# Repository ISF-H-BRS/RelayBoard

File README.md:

# ISF Relay Board

## Introduction
This repository contains schematics, PCB layout, firmware and software for a circuit board providing 16 software-programmable solid-state relays with individual voltage and current monitoring, every channel capable of switching up to 2 A at 32 V. It's original purpose was to allow control of various valves and pumps for chemical processes from within a LabVIEW program but it may also be useful for other automated control tasks.

## Usage
The device uses a simple text-based protocol to communicate over a USB serial port. See Firmware/Protocol.txt for details. The protocol is also wrapped in a software library exposing both C++ and C interfaces, designed to allow it to be used from any programming language, including LabVIEW.

A Qt-based graphical example program is also provided that can be used to manually test all features of the device.

## License
All source code for the software and firmware components, including the LabVIEW code, is licensed under the terms of the GNU General Public License (GPL). All schematics and layout files are licensed under the terms of the Creative Commons Attribution-ShareAlike International Public License (CC BY-SA). See COPYING in the respective subdirectories for details.

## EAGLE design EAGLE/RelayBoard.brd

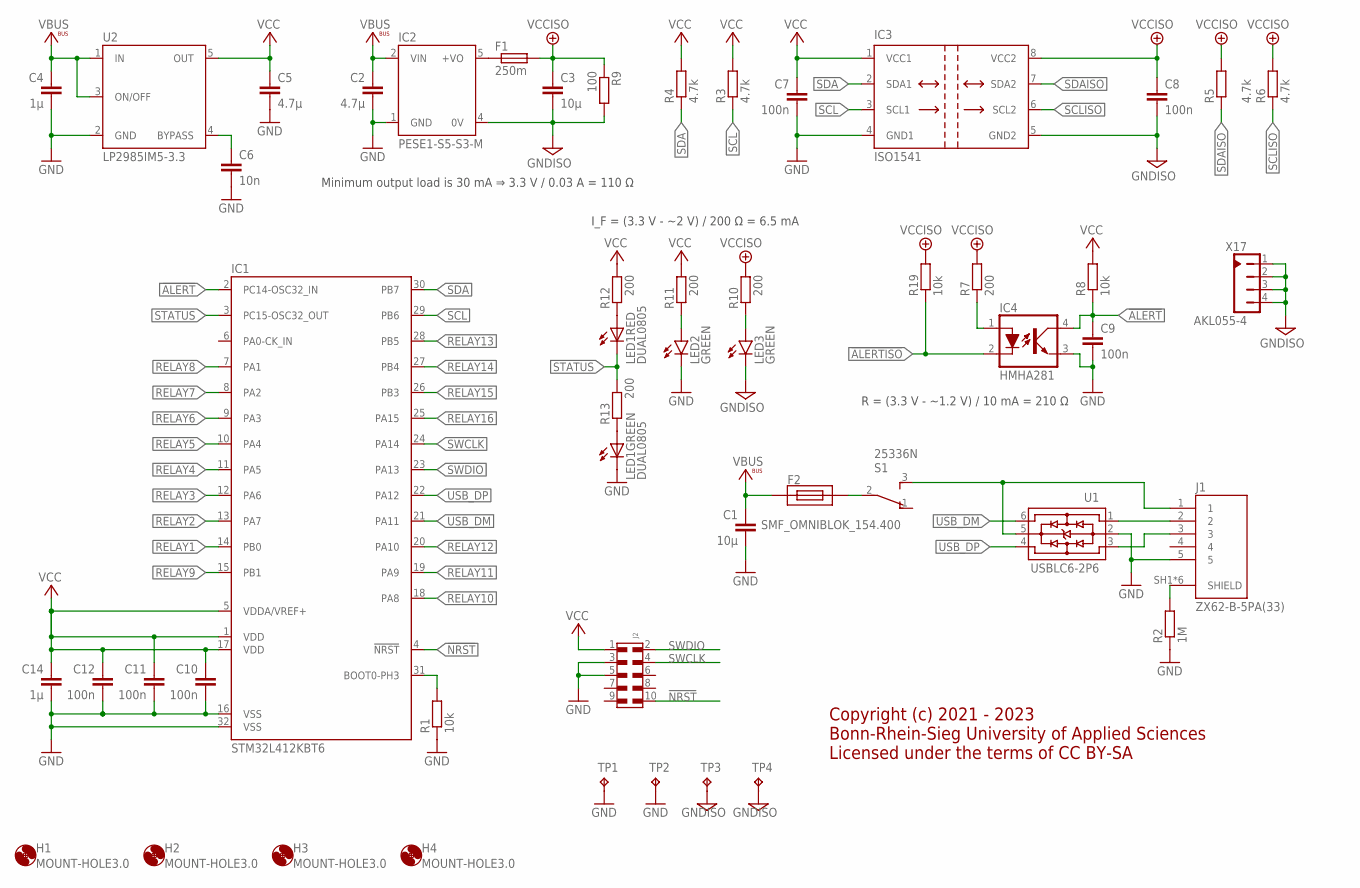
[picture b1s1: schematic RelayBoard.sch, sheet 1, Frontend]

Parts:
C1, C3: 10µ; C0805
C2, C5: 4.7µ; C0805
C4: 1µ; C0805
C6: 10n; C0603
C7, C8, C9, C10, C11, C12: 100n; C0603
C14: 1µ; C0603
F1: 250m; R0603
F2: SMF_OMNIBLOK_154.400; NANO2_SMF_FUSEBLOCK
H1, H2, H3, H4: MOUNT-HOLE3.0; 3,0
IC1: STM32L412KBT6; LQFP32
IC2: PESE1-S5-S3-M; PESE1-M
IC3: ISO1541; SOIC8
IC4: HMHA281; 4-MINI-FLAT
J1: ZX62-B-5PA(33); HRS_ZX62-B-5PA(33)
J2: 6210XX21021_62101021021; 62101021021
LED1: DUAL0805; CHIPLEDX2
LED2, LED3: GREEN; CHIPLED_0805
R1, R8, R19: 10k; R0603
R2: 1M; R0603
R3, R4, R5, R6: 4.7k; R0603
R7, R10, R11, R12, R13: 200; R0603
R9: 100; R0603
S1: 25336N; 2533XN
TP1, TP2, TP3, TP4: TP3.8X2.03; 3.8X2.03
U1: USBLC6-2P6; SOT-666
U2: LP2985IM5-3.3; SOT23-5
X17: AKL055-4

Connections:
!ALERT: C9.1, IC1.2 (PC14-OSC32_IN), IC4.4 (COLLECTOR), R8.1
!ALERTISO: IC4.2 (CATHODE), R19.1; also elsewhere on the board
!NRST: IC1.4 (!NRST), J2.10
GND: C1.2, C2.2, C4.2, C5.2, C6.2, C7.2, C9.2, C10.2, C11.2, C12.2, C14.2, IC1.16 (VSS), IC1.32 (VSS), IC2.1 (GND), IC3.4 (GND1), IC4.3 (EMITTER), J1.5, J2.3, J2.5, LED1.C2 (C), LED2.C, R1.1, R2.1, TP1.TP, TP2.TP, U1.2, U2.2 (GND); also elsewhere on the board
GNDISO: C3.2, C8.2, IC2.4 (0V), IC3.5 (GND2), LED3.C, R9.2, TP3.TP, TP4.TP, X17.1, X17.2, X17.3, X17.4; also elsewhere on the board
unnamed: J1.2, U1.1
unnamed: J1.3, U1.3
unnamed: J1.SH1 (SHIELD), J1.SH2 (SHIELD), J1.SH3 (SHIELD), J1.SH4 (SHIELD), J1.SH5 (SHIELD), J1.SH6 (SHIELD), R2.2
unnamed: IC4.1 (ANODE), R7.1
unnamed: C6.1, U2.4 (BYPASS)
unnamed: IC1.31 (BOOT0-PH3), R1.2
unnamed: LED3.A, R10.1
unnamed: LED2.A, R11.1
unnamed: LED1.A2 (A), R13.1
unnamed: LED1.A1 (A), R12.1
unnamed: J1.1, S1.3, U1.5
unnamed: F2.2, S1.2
unnamed: F1.1, IC2.5 (+VO)
RELAY1: IC1.14 (PB0); also elsewhere on the board
RELAY2: IC1.13 (PA7); also elsewhere on the board
RELAY3: IC1.12 (PA6); also elsewhere on the board
RELAY4: IC1.11 (PA5); also elsewhere on the board
RELAY5: IC1.10 (PA4); also elsewhere on the board
RELAY6: IC1.9 (PA3); also elsewhere on the board
RELAY7: IC1.8 (PA2); also elsewhere on the board
RELAY8: IC1.7 (PA1); also elsewhere on the board
RELAY9: IC1.15 (PB1); also elsewhere on the board
RELAY10: IC1.18 (PA8); also elsewhere on the board
RELAY11: IC1.19 (PA9); also elsewhere on the board
RELAY12: IC1.20 (PA10); also elsewhere on the board
RELAY13: IC1.28 (PB5); also elsewhere on the board
RELAY14: IC1.27 (PB4); also elsewhere on the board
RELAY15: IC1.26 (PB3); also elsewhere on the board
RELAY16: IC1.25 (PA15); also elsewhere on the board
SCL: IC1.29 (PB6), IC3.3 (SCL1), R3.1
SCLISO: IC3.6 (SCL2), R6.1; also elsewhere on the board
SDA: IC1.30 (PB7), IC3.2 (SDA1), R4.1
SDAISO: IC3.7 (SDA2), R5.1; also elsewhere on the board
STATUS: IC1.3 (PC15-OSC32_OUT), LED1.C1 (C), R13.2
SWCLK: IC1.24 (PA14), J2.4
SWDIO: IC1.23 (PA13), J2.2
USB_DM: IC1.21 (PA11), U1.6
USB_DP: IC1.22 (PA12), U1.4
VBUS: C1.1, C2.1, C4.1, F2.1, IC2.2 (VIN), U2.1 (IN), U2.3 (ON/OFF); also elsewhere on the board
VCC: C5.1, C7.1, C10.1, C11.1, C12.1, C14.1, IC1.1 (VDD), IC1.5 (VDDA/VREF+), IC1.17 (VDD), IC3.1 (VCC1), J2.1, R3.2, R4.2, R8.2, R11.2, R12.2, U2.5 (OUT)
VCCISO: C3.1, C8.1, F1.2, IC3.8 (VCC2), R5.2, R6.2, R7.2, R9.1, R10.2, R19.2; also elsewhere on the board

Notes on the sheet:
R = (3.3 V - ~1.2 V) / 10 mA = 210 Ω
Minimum output load is 30 mA ⇒ 3.3 V / 0.03 A = 110 Ω
I_F = (3.3 V - ~2 V) / 200 Ω = 6.5 mA
Copyright (c) 2021 - 2023 Bonn-Rhein-Sieg University of Applied Sciences Licensed under the terms of CC BY-SA

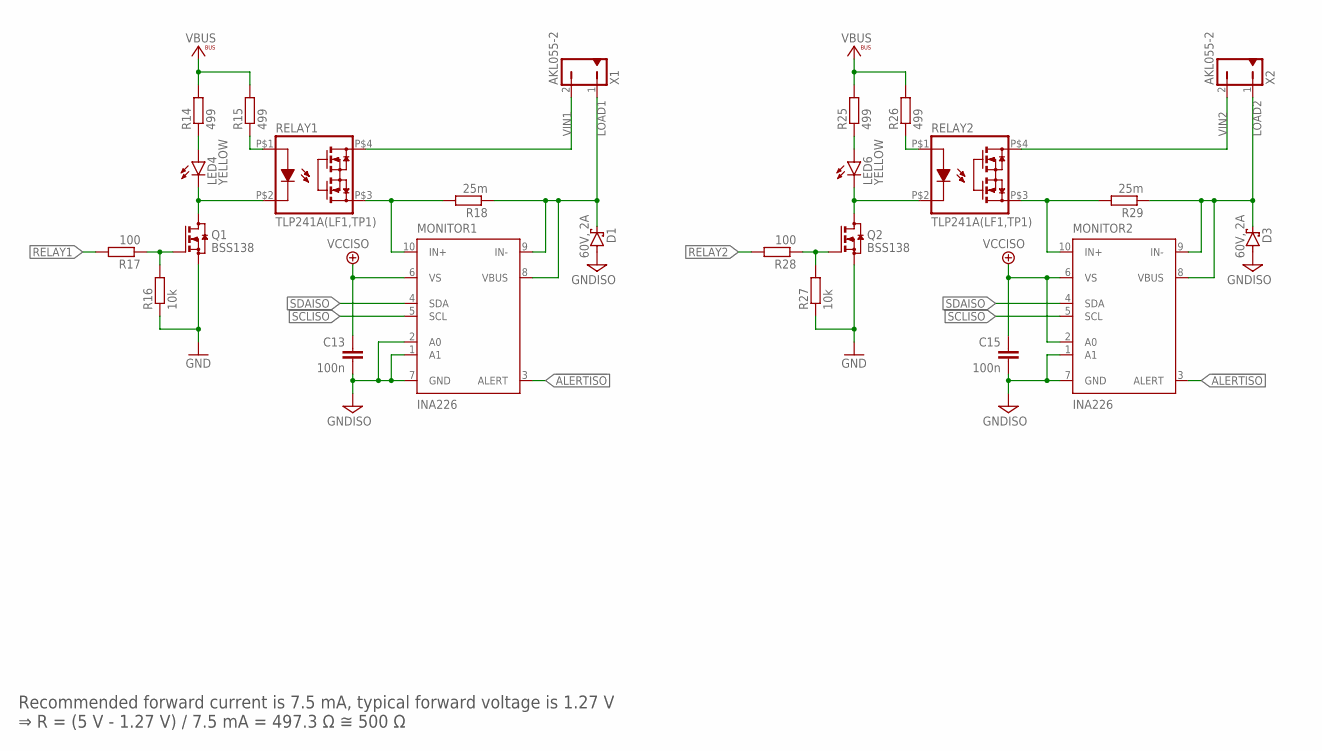
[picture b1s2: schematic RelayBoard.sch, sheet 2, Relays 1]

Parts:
C13, C15: 100n; C0603
D1, D3: 60V, 2A; SMB
LED4, LED6: YELLOW; CHIPLED_0805
MONITOR1, MONITOR2: INA226; MSOP10
Q1, Q2: BSS138; SOT23
R14, R15, R25, R26: 499; R0603
R16, R27: 10k; R0603
R17, R28: 100; R0603
R18, R29: 25m; R1206
RELAY1, RELAY2: TLP241A(LF1,TP1); TP1/5
X1, X2: AKL055-2

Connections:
!ALERTISO: MONITOR1.3 (ALERT), MONITOR2.3 (ALERT); also elsewhere on the board
GND: Q1.2 (S), Q2.2 (S), R16.1, R27.1; also elsewhere on the board
GNDISO: C13.2, C15.2, D1.A, D3.A, MONITOR1.1 (A1), MONITOR1.2 (A0), MONITOR1.7 (GND), MONITOR2.1 (A1), MONITOR2.7 (GND); also elsewhere on the board
LOAD1: D1.C, MONITOR1.8 (VBUS), MONITOR1.9 (IN-), R18.1, X1.1
LOAD2: D3.C, MONITOR2.8 (VBUS), MONITOR2.9 (IN-), R29.1, X2.1
unnamed: LED4.A, R14.1
unnamed: LED4.C, Q1.3 (D), RELAY1.P$2 (CATHODE)
unnamed: Q1.1 (G), R16.2, R17.1
unnamed: MONITOR1.10 (IN+), R18.2, RELAY1.P$3 (DRAIN1)
unnamed: R15.1, RELAY1.P$1 (ANODE)
unnamed: LED6.A, R25.1
unnamed: LED6.C, Q2.3 (D), RELAY2.P$2 (CATHODE)
unnamed: Q2.1 (G), R27.2, R28.1
unnamed: MONITOR2.10 (IN+), R29.2, RELAY2.P$3 (DRAIN1)
unnamed: R26.1, RELAY2.P$1 (ANODE)
RELAY1: R17.2; also elsewhere on the board
RELAY2: R28.2; also elsewhere on the board
SCLISO: MONITOR1.5 (SCL), MONITOR2.5 (SCL); also elsewhere on the board
SDAISO: MONITOR1.4 (SDA), MONITOR2.4 (SDA); also elsewhere on the board
VBUS: R14.2, R15.2, R25.2, R26.2; also elsewhere on the board
VCCISO: C13.1, C15.1, MONITOR1.6 (VS), MONITOR2.2 (A0), MONITOR2.6 (VS); also elsewhere on the board
VIN1: RELAY1.P$4 (DRAIN2), X1.2 (4)
VIN2: RELAY2.P$4 (DRAIN2), X2.2 (4)

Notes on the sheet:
Recommended forward current is 7.5 mA, typical forward voltage is 1.27 V ⇒ R = (5 V - 1.27 V) / 7.5 mA = 497.3 Ω ≅ 500 Ω

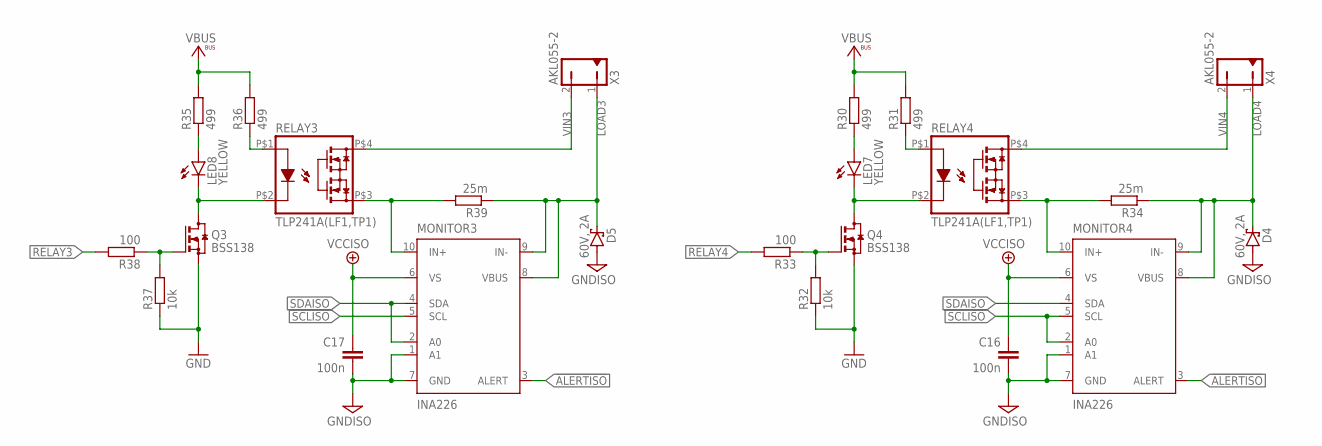
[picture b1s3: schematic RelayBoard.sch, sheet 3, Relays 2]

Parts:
C16, C17: 100n; C0603
D4, D5: 60V, 2A; SMB
LED7, LED8: YELLOW; CHIPLED_0805
MONITOR3, MONITOR4: INA226; MSOP10
Q3, Q4: BSS138; SOT23
R30, R31, R35, R36: 499; R0603
R32, R37: 10k; R0603
R33, R38: 100; R0603
R34, R39: 25m; R1206
RELAY3, RELAY4: TLP241A(LF1,TP1); TP1/5
X3, X4: AKL055-2

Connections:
!ALERTISO: MONITOR3.3 (ALERT), MONITOR4.3 (ALERT); also elsewhere on the board
GND: Q3.2 (S), Q4.2 (S), R32.1, R37.1; also elsewhere on the board
GNDISO: C16.2, C17.2, D4.A, D5.A, MONITOR3.1 (A1), MONITOR3.7 (GND), MONITOR4.1 (A1), MONITOR4.7 (GND); also elsewhere on the board
LOAD3: D5.C, MONITOR3.8 (VBUS), MONITOR3.9 (IN-), R39.1, X3.1
LOAD4: D4.C, MONITOR4.8 (VBUS), MONITOR4.9 (IN-), R34.1, X4.1
unnamed: LED7.A, R30.1
unnamed: LED7.C, Q4.3 (D), RELAY4.P$2 (CATHODE)
unnamed: Q4.1 (G), R32.2, R33.1
unnamed: MONITOR4.10 (IN+), R34.2, RELAY4.P$3 (DRAIN1)
unnamed: R31.1, RELAY4.P$1 (ANODE)
unnamed: LED8.A, R35.1
unnamed: LED8.C, Q3.3 (D), RELAY3.P$2 (CATHODE)
unnamed: Q3.1 (G), R37.2, R38.1
unnamed: MONITOR3.10 (IN+), R39.2, RELAY3.P$3 (DRAIN1)
unnamed: R36.1, RELAY3.P$1 (ANODE)
RELAY3: R38.2; also elsewhere on the board
RELAY4: R33.2; also elsewhere on the board
SCLISO: MONITOR3.5 (SCL), MONITOR4.2 (A0), MONITOR4.5 (SCL); also elsewhere on the board
SDAISO: MONITOR3.2 (A0), MONITOR3.4 (SDA), MONITOR4.4 (SDA); also elsewhere on the board
VBUS: R30.2, R31.2, R35.2, R36.2; also elsewhere on the board
VCCISO: C16.1, C17.1, MONITOR3.6 (VS), MONITOR4.6 (VS); also elsewhere on the board
VIN3: RELAY3.P$4 (DRAIN2), X3.2 (4)
VIN4: RELAY4.P$4 (DRAIN2), X4.2 (4)

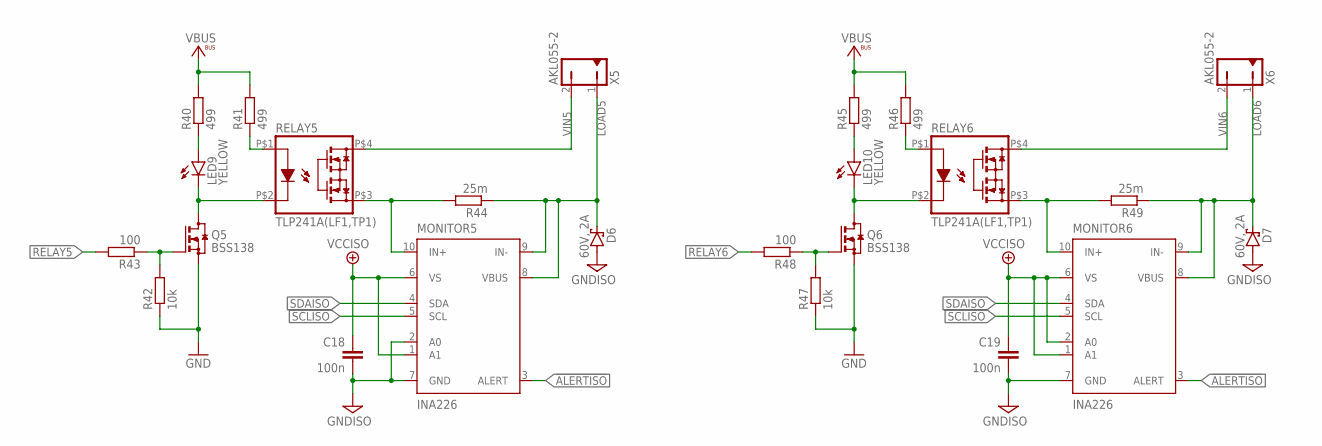
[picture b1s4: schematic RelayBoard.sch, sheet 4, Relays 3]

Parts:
C18, C19: 100n; C0603
D6, D7: 60V, 2A; SMB
LED9, LED10: YELLOW; CHIPLED_0805
MONITOR5, MONITOR6: INA226; MSOP10
Q5, Q6: BSS138; SOT23
R40, R41, R45, R46: 499; R0603
R42, R47: 10k; R0603
R43, R48: 100; R0603
R44, R49: 25m; R1206
RELAY5, RELAY6: TLP241A(LF1,TP1); TP1/5
X5, X6: AKL055-2

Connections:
!ALERTISO: MONITOR5.3 (ALERT), MONITOR6.3 (ALERT); also elsewhere on the board
GND: Q5.2 (S), Q6.2 (S), R42.1, R47.1; also elsewhere on the board
GNDISO: C18.2, C19.2, D6.A, D7.A, MONITOR5.2 (A0), MONITOR5.7 (GND), MONITOR6.7 (GND); also elsewhere on the board
LOAD5: D6.C, MONITOR5.8 (VBUS), MONITOR5.9 (IN-), R44.1, X5.1
LOAD6: D7.C, MONITOR6.8 (VBUS), MONITOR6.9 (IN-), R49.1, X6.1
unnamed: LED9.A, R40.1
unnamed: LED9.C, Q5.3 (D), RELAY5.P$2 (CATHODE)
unnamed: Q5.1 (G), R42.2, R43.1
unnamed: MONITOR5.10 (IN+), R44.2, RELAY5.P$3 (DRAIN1)
unnamed: R41.1, RELAY5.P$1 (ANODE)
unnamed: LED10.A, R45.1
unnamed: LED10.C, Q6.3 (D), RELAY6.P$2 (CATHODE)
unnamed: Q6.1 (G), R47.2, R48.1
unnamed: MONITOR6.10 (IN+), R49.2, RELAY6.P$3 (DRAIN1)
unnamed: R46.1, RELAY6.P$1 (ANODE)
RELAY5: R43.2; also elsewhere on the board
RELAY6: R48.2; also elsewhere on the board
SCLISO: MONITOR5.5 (SCL), MONITOR6.5 (SCL); also elsewhere on the board
SDAISO: MONITOR5.4 (SDA), MONITOR6.4 (SDA); also elsewhere on the board
VBUS: R40.2, R41.2, R45.2, R46.2; also elsewhere on the board
VCCISO: C18.1, C19.1, MONITOR5.1 (A1), MONITOR5.6 (VS), MONITOR6.1 (A1), MONITOR6.2 (A0), MONITOR6.6 (VS); also elsewhere on the board
VIN5: RELAY5.P$4 (DRAIN2), X5.2 (4)
VIN6: RELAY6.P$4 (DRAIN2), X6.2 (4)

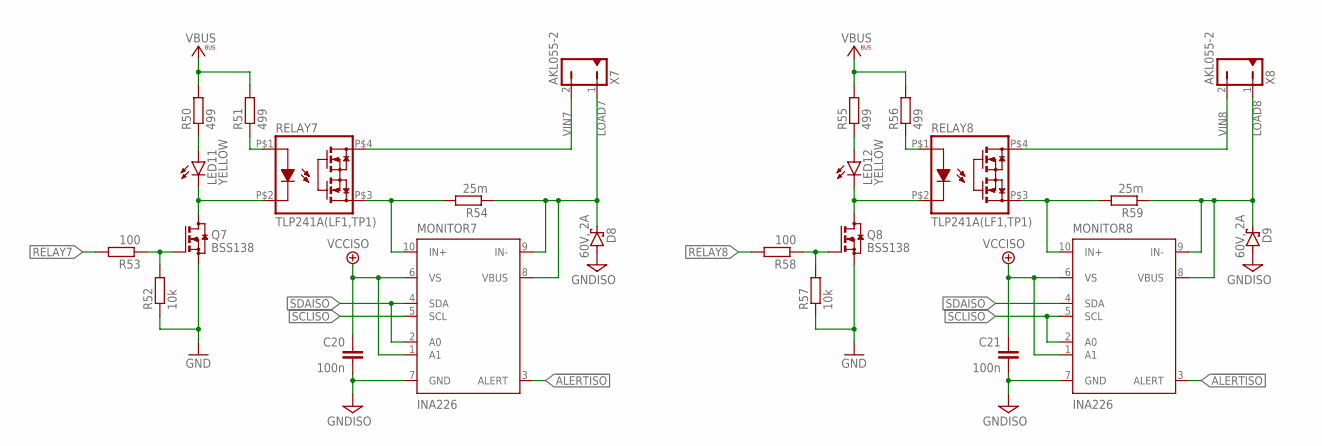
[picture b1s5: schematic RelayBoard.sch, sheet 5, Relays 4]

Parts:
C20, C21: 100n; C0603
D8, D9: 60V, 2A; SMB
LED11, LED12: YELLOW; CHIPLED_0805
MONITOR7, MONITOR8: INA226; MSOP10
Q7, Q8: BSS138; SOT23
R50, R51, R55, R56: 499; R0603
R52, R57: 10k; R0603
R53, R58: 100; R0603
R54, R59: 25m; R1206
RELAY7, RELAY8: TLP241A(LF1,TP1); TP1/5
X7, X8: AKL055-2

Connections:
!ALERTISO: MONITOR7.3 (ALERT), MONITOR8.3 (ALERT); also elsewhere on the board
GND: Q7.2 (S), Q8.2 (S), R52.1, R57.1; also elsewhere on the board
GNDISO: C20.2, C21.2, D8.A, D9.A, MONITOR7.7 (GND), MONITOR8.7 (GND); also elsewhere on the board
LOAD7: D8.C, MONITOR7.8 (VBUS), MONITOR7.9 (IN-), R54.1, X7.1
LOAD8: D9.C, MONITOR8.8 (VBUS), MONITOR8.9 (IN-), R59.1, X8.1
unnamed: LED11.A, R50.1
unnamed: LED11.C, Q7.3 (D), RELAY7.P$2 (CATHODE)
unnamed: Q7.1 (G), R52.2, R53.1
unnamed: MONITOR7.10 (IN+), R54.2, RELAY7.P$3 (DRAIN1)
unnamed: R51.1, RELAY7.P$1 (ANODE)
unnamed: LED12.A, R55.1
unnamed: LED12.C, Q8.3 (D), RELAY8.P$2 (CATHODE)
unnamed: Q8.1 (G), R57.2, R58.1
unnamed: MONITOR8.10 (IN+), R59.2, RELAY8.P$3 (DRAIN1)
unnamed: R56.1, RELAY8.P$1 (ANODE)
RELAY7: R53.2; also elsewhere on the board
RELAY8: R58.2; also elsewhere on the board
SCLISO: MONITOR7.5 (SCL), MONITOR8.2 (A0), MONITOR8.5 (SCL); also elsewhere on the board
SDAISO: MONITOR7.2 (A0), MONITOR7.4 (SDA), MONITOR8.4 (SDA); also elsewhere on the board
VBUS: R50.2, R51.2, R55.2, R56.2; also elsewhere on the board
VCCISO: C20.1, C21.1, MONITOR7.1 (A1), MONITOR7.6 (VS), MONITOR8.1 (A1), MONITOR8.6 (VS); also elsewhere on the board
VIN7: RELAY7.P$4 (DRAIN2), X7.2 (4)
VIN8: RELAY8.P$4 (DRAIN2), X8.2 (4)

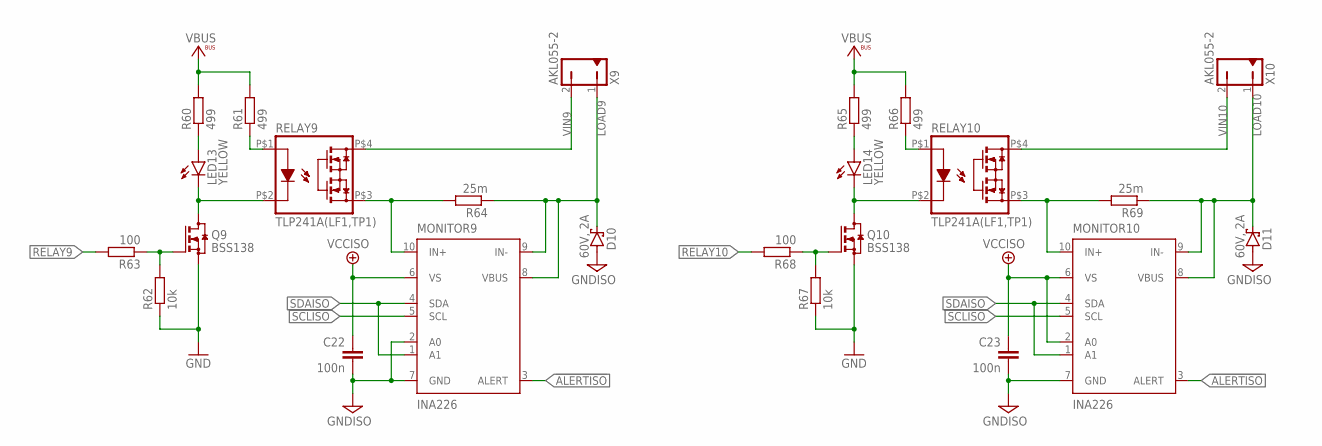
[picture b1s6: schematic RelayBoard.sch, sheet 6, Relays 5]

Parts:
C22, C23: 100n; C0603
D10, D11: 60V, 2A; SMB
LED13, LED14: YELLOW; CHIPLED_0805
MONITOR9, MONITOR10: INA226; MSOP10
Q9, Q10: BSS138; SOT23
R60, R61, R65, R66: 499; R0603
R62, R67: 10k; R0603
R63, R68: 100; R0603
R64, R69: 25m; R1206
RELAY9, RELAY10: TLP241A(LF1,TP1); TP1/5
X9, X10: AKL055-2

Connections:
!ALERTISO: MONITOR9.3 (ALERT), MONITOR10.3 (ALERT); also elsewhere on the board
GND: Q9.2 (S), Q10.2 (S), R62.1, R67.1; also elsewhere on the board
GNDISO: C22.2, C23.2, D10.A, D11.A, MONITOR9.2 (A0), MONITOR9.7 (GND), MONITOR10.7 (GND); also elsewhere on the board
LOAD9: D10.C, MONITOR9.8 (VBUS), MONITOR9.9 (IN-), R64.1, X9.1
LOAD10: D11.C, MONITOR10.8 (VBUS), MONITOR10.9 (IN-), R69.1, X10.1
unnamed: LED13.A, R60.1
unnamed: LED13.C, Q9.3 (D), RELAY9.P$2 (CATHODE)
unnamed: Q9.1 (G), R62.2, R63.1
unnamed: MONITOR9.10 (IN+), R64.2, RELAY9.P$3 (DRAIN1)
unnamed: R61.1, RELAY9.P$1 (ANODE)
unnamed: LED14.A, R65.1
unnamed: LED14.C, Q10.3 (D), RELAY10.P$2 (CATHODE)
unnamed: Q10.1 (G), R67.2, R68.1
unnamed: MONITOR10.10 (IN+), R69.2, RELAY10.P$3 (DRAIN1)
unnamed: R66.1, RELAY10.P$1 (ANODE)
RELAY9: R63.2; also elsewhere on the board
RELAY10: R68.2; also elsewhere on the board
SCLISO: MONITOR9.5 (SCL), MONITOR10.5 (SCL); also elsewhere on the board
SDAISO: MONITOR9.1 (A1), MONITOR9.4 (SDA), MONITOR10.1 (A1), MONITOR10.4 (SDA); also elsewhere on the board
VBUS: R60.2, R61.2, R65.2, R66.2; also elsewhere on the board
VCCISO: C22.1, C23.1, MONITOR9.6 (VS), MONITOR10.2 (A0), MONITOR10.6 (VS); also elsewhere on the board
VIN9: RELAY9.P$4 (DRAIN2), X9.2 (4)
VIN10: RELAY10.P$4 (DRAIN2), X10.2 (4)

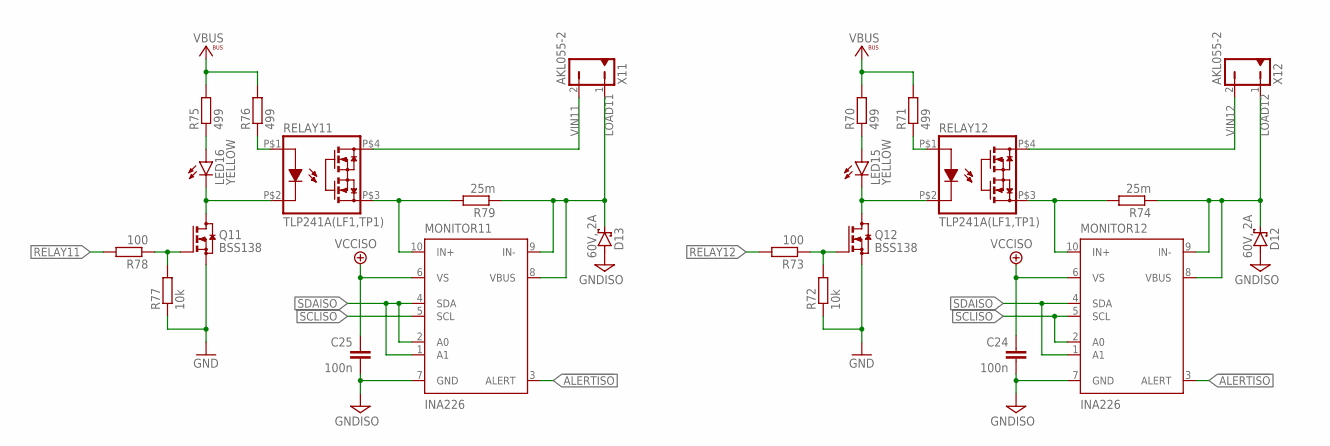
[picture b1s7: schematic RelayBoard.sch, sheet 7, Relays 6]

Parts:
C24, C25: 100n; C0603
D12, D13: 60V, 2A; SMB
LED15, LED16: YELLOW; CHIPLED_0805
MONITOR11, MONITOR12: INA226; MSOP10
Q11, Q12: BSS138; SOT23
R70, R71, R75, R76: 499; R0603
R72, R77: 10k; R0603
R73, R78: 100; R0603
R74, R79: 25m; R1206
RELAY11, RELAY12: TLP241A(LF1,TP1); TP1/5
X11, X12: AKL055-2

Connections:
!ALERTISO: MONITOR11.3 (ALERT), MONITOR12.3 (ALERT); also elsewhere on the board
GND: Q11.2 (S), Q12.2 (S), R72.1, R77.1; also elsewhere on the board
GNDISO: C24.2, C25.2, D12.A, D13.A, MONITOR11.7 (GND), MONITOR12.7 (GND); also elsewhere on the board
LOAD11: D13.C, MONITOR11.8 (VBUS), MONITOR11.9 (IN-), R79.1, X11.1
LOAD12: D12.C, MONITOR12.8 (VBUS), MONITOR12.9 (IN-), R74.1, X12.1
unnamed: LED15.A, R70.1
unnamed: LED15.C, Q12.3 (D), RELAY12.P$2 (CATHODE)
unnamed: Q12.1 (G), R72.2, R73.1
unnamed: MONITOR12.10 (IN+), R74.2, RELAY12.P$3 (DRAIN1)
unnamed: R71.1, RELAY12.P$1 (ANODE)
unnamed: LED16.A, R75.1
unnamed: LED16.C, Q11.3 (D), RELAY11.P$2 (CATHODE)
unnamed: Q11.1 (G), R77.2, R78.1
unnamed: MONITOR11.10 (IN+), R79.2, RELAY11.P$3 (DRAIN1)
unnamed: R76.1, RELAY11.P$1 (ANODE)
RELAY11: R78.2; also elsewhere on the board
RELAY12: R73.2; also elsewhere on the board
SCLISO: MONITOR11.5 (SCL), MONITOR12.2 (A0), MONITOR12.5 (SCL); also elsewhere on the board
SDAISO: MONITOR11.1 (A1), MONITOR11.2 (A0), MONITOR11.4 (SDA), MONITOR12.1 (A1), MONITOR12.4 (SDA); also elsewhere on the board
VBUS: R70.2, R71.2, R75.2, R76.2; also elsewhere on the board
VCCISO: C24.1, C25.1, MONITOR11.6 (VS), MONITOR12.6 (VS); also elsewhere on the board
VIN11: RELAY11.P$4 (DRAIN2), X11.2 (4)
VIN12: RELAY12.P$4 (DRAIN2), X12.2 (4)

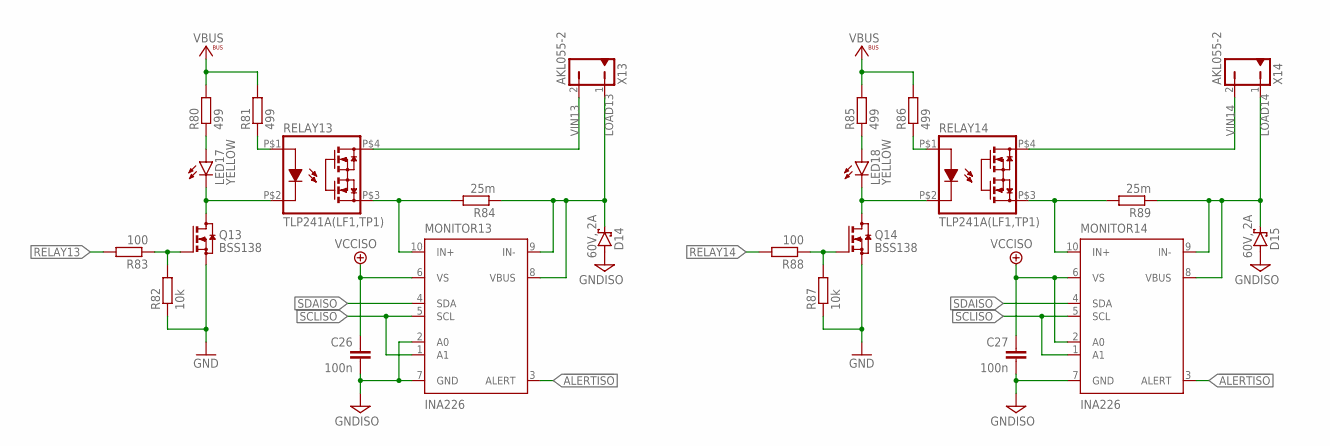
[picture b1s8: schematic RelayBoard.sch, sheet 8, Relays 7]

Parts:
C26, C27: 100n; C0603
D14, D15: 60V, 2A; SMB
LED17, LED18: YELLOW; CHIPLED_0805
MONITOR13, MONITOR14: INA226; MSOP10
Q13, Q14: BSS138; SOT23
R80, R81, R85, R86: 499; R0603
R82, R87: 10k; R0603
R83, R88: 100; R0603
R84, R89: 25m; R1206
RELAY13, RELAY14: TLP241A(LF1,TP1); TP1/5
X13, X14: AKL055-2

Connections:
!ALERTISO: MONITOR13.3 (ALERT), MONITOR14.3 (ALERT); also elsewhere on the board
GND: Q13.2 (S), Q14.2 (S), R82.1, R87.1; also elsewhere on the board
GNDISO: C26.2, C27.2, D14.A, D15.A, MONITOR13.2 (A0), MONITOR13.7 (GND), MONITOR14.7 (GND); also elsewhere on the board
LOAD13: D14.C, MONITOR13.8 (VBUS), MONITOR13.9 (IN-), R84.1, X13.1
LOAD14: D15.C, MONITOR14.8 (VBUS), MONITOR14.9 (IN-), R89.1, X14.1
unnamed: LED17.A, R80.1
unnamed: LED17.C, Q13.3 (D), RELAY13.P$2 (CATHODE)
unnamed: Q13.1 (G), R82.2, R83.1
unnamed: MONITOR13.10 (IN+), R84.2, RELAY13.P$3 (DRAIN1)
unnamed: R81.1, RELAY13.P$1 (ANODE)
unnamed: LED18.A, R85.1
unnamed: LED18.C, Q14.3 (D), RELAY14.P$2 (CATHODE)
unnamed: Q14.1 (G), R87.2, R88.1
unnamed: MONITOR14.10 (IN+), R89.2, RELAY14.P$3 (DRAIN1)
unnamed: R86.1, RELAY14.P$1 (ANODE)
RELAY13: R83.2; also elsewhere on the board
RELAY14: R88.2; also elsewhere on the board
SCLISO: MONITOR13.1 (A1), MONITOR13.5 (SCL), MONITOR14.1 (A1), MONITOR14.5 (SCL); also elsewhere on the board
SDAISO: MONITOR13.4 (SDA), MONITOR14.4 (SDA); also elsewhere on the board
VBUS: R80.2, R81.2, R85.2, R86.2; also elsewhere on the board
VCCISO: C26.1, C27.1, MONITOR13.6 (VS), MONITOR14.2 (A0), MONITOR14.6 (VS); also elsewhere on the board
VIN13: RELAY13.P$4 (DRAIN2), X13.2 (4)
VIN14: RELAY14.P$4 (DRAIN2), X14.2 (4)

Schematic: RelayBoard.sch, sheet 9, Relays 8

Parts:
C28, C30: 100n; C0603
D16, D18: 60V, 2A; SMB
LED19, LED21: YELLOW; CHIPLED_0805
MONITOR15, MONITOR16: INA226; MSOP10
Q15, Q16: BSS138; SOT23
R90, R91, R100, R101: 499; R0603
R92, R102: 10k; R0603
R93, R103: 100; R0603
R94, R104: 25m; R1206
RELAY15, RELAY16: TLP241A(LF1,TP1); TP1/5
X15, X16: AKL055-2

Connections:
!ALERTISO: MONITOR15.3 (ALERT), MONITOR16.3 (ALERT); also elsewhere on the board
GND: Q15.2 (S), Q16.2 (S), R92.1, R102.1; also elsewhere on the board
GNDISO: C28.2, C30.2, D16.A, D18.A, MONITOR15.7 (GND), MONITOR16.7 (GND); also elsewhere on the board
LOAD15: D16.C, MONITOR15.8 (VBUS), MONITOR15.9 (IN-), R94.1, X15.1
LOAD16: D18.C, MONITOR16.8 (VBUS), MONITOR16.9 (IN-), R104.1, X16.1
unnamed: LED19.A, R90.1
unnamed: LED19.C, Q15.3 (D), RELAY15.P$2 (CATHODE)
unnamed: Q15.1 (G), R92.2, R93.1
unnamed: MONITOR15.10 (IN+), R94.2, RELAY15.P$3 (DRAIN1)
unnamed: R91.1, RELAY15.P$1 (ANODE)
unnamed: LED21.A, R100.1
unnamed: LED21.C, Q16.3 (D), RELAY16.P$2 (CATHODE)
unnamed: Q16.1 (G), R102.2, R103.1
unnamed: MONITOR16.10 (IN+), R104.2, RELAY16.P$3 (DRAIN1)
unnamed: R101.1, RELAY16.P$1 (ANODE)
RELAY15: R93.2; also elsewhere on the board
RELAY16: R103.2; also elsewhere on the board
SCLISO: MONITOR15.1 (A1), MONITOR15.5 (SCL), MONITOR16.1 (A1), MONITOR16.2 (A0), MONITOR16.5 (SCL); also elsewhere on the board
SDAISO: MONITOR15.2 (A0), MONITOR15.4 (SDA), MONITOR16.4 (SDA); also elsewhere on the board
VBUS: R90.2, R91.2, R100.2, R101.2; also elsewhere on the board
VCCISO: C28.1, C30.1, MONITOR15.6 (VS), MONITOR16.6 (VS); also elsewhere on the board
VIN15: RELAY15.P$4 (DRAIN2), X15.2 (4)
VIN16: RELAY16.P$4 (DRAIN2), X16.2 (4)

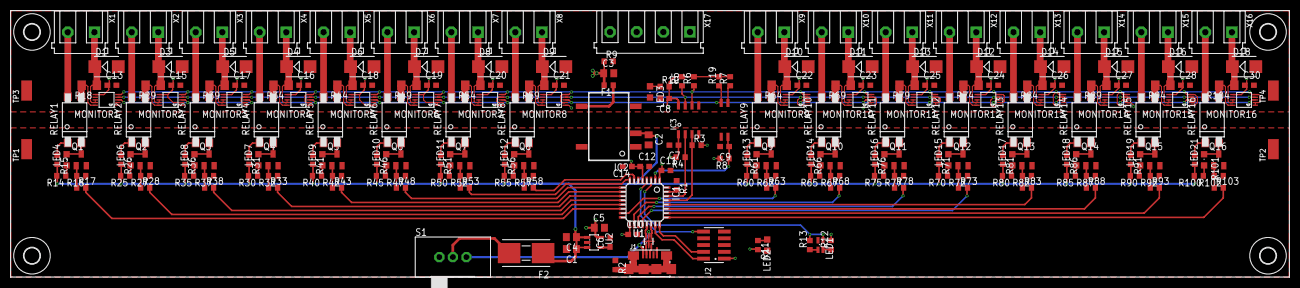
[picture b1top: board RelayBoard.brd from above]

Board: 2 copper layers, 240.0 x 50.0 mm, 242 parts (0 on the bottom side), 158 nets.

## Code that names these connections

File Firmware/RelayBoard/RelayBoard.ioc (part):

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PA15\ (JTDI).GPIOParameters=GPIO_Label
PA14\ (JTCK/SWCLK).GPIOParameters=GPIO_Label
PC14-OSC32_IN\ (PC14).GPIO_PuPd=GPIO_PULLUP
Mcu.UserName=STM32L412KBTx
PA9.GPIOParameters=GPIO_Label
PA11.Mode=Device
PA3.GPIOParameters=GPIO_Label
PA6.GPIO_Label=RELAY03
PB0.GPIO_Label=RELAY01
PB6.GPIO_Label=SCL
PA15\ (JTDI).Signal=GPIO_Output
PB3\ (JTDO/TRACESWO).GPIOParameters=GPIO_Label
PA2.GPIOParameters=GPIO_Label
RCC.SYSCLKSource=RCC_SYSCLKSOURCE_PLLCLK
PB5.GPIOParameters=GPIO_Label
PA14\ (JTCK/SWCLK).Signal=SYS_JTCK-SWCLK
PA12.Signal=USB_DP
PC15-OSC32_OUT\ (PC15).GPIOParameters=PinState,GPIO_Label
PB6.Signal=I2C1_SCL
PB6.Mode=I2C
PA8.GPIOParameters=GPIO_Label
RCC.HSE_VALUE=8000000
PB0.GPIOParameters=GPIO_Label
PA13\ (JTMS/SWDIO).GPIO_Label=SWDIO
PA1.GPIOParameters=GPIO_Label
PB1.GPIO_Label=RELAY09
PA10.GPIO_Label=RELAY12
PB7.Signal=I2C1_SDA
PA8.Signal=GPIO_Output
PA14\ (JTCK/SWCLK).Mode=Serial_Wire
PB6.GPIOParameters=GPIO_Label
PC15-OSC32_OUT\ (PC15).PinState=GPIO_PIN_RESET
PB7.GPIO_Label=SDA
Mcu.Package=LQFP32
PB1.Signal=GPIO_Output
PA6.Signal=GPIO_Output
PA2.GPIO_Label=RELAY07
PA10.Signal=GPIO_Output
PA5.GPIOParameters=GPIO_Label
PA14\ (JTCK/SWCLK).GPIO_Label=SWCLK
PB5.GPIO_Label=RELAY13
PA4.GPIO_Label=RELAY05
PA3.Signal=GPIO_Output
PA6.GPIOParameters=GPIO_Label
PB3\ (JTDO/TRACESWO).GPIO_Label=RELAY15
PC15-OSC32_OUT\ (PC15).GPIO_Label=STATUS
PA13\ (JTMS/SWDIO).Mode=Serial_Wire
PA9.GPIO_Label=RELAY11
PC15-OSC32_OUT\ (PC15).Signal=GPIO_Output
PA13\ (JTMS/SWDIO).GPIOParameters=GPIO_Label
PC14-OSC32_IN\ (PC14).GPIO_Label=ALERT
PB4\ (NJTRST).GPIOParameters=GPIO_Label
PA8.GPIO_Label=RELAY10
PB3\ (JTDO/TRACESWO).Signal=GPIO_Output
PB7.GPIOParameters=GPIO_Label
PA9.Signal=GPIO_Output
PA1.Signal=GPIO_Output
PA5.Signal=GPIO_Output
board=custom
PA1.GPIO_Label=RELAY08
PA10.GPIOParameters=GPIO_Label
PA4.GPIOParameters=GPIO_Label
PA15\ (JTDI).GPIO_Label=RELAY16
Mcu.Name=STM32L412KBTx
PA2.Signal=GPIO_Output
PA4.Signal=GPIO_Output
RCC.SYSCLKFreq_VALUE=80000000
PB5.Signal=GPIO_Output
PA7.GPIO_Label=RELAY02
PA12.Mode=Device
PA5.GPIO_Label=RELAY04
PC14-OSC32_IN\ (PC14).Signal=GPIO_Input
PB7.Mode=I2C
PA11.Signal=USB_DM
PC14-OSC32_IN\ (PC14).GPIOParameters=GPIO_PuPd,GPIO_Label
PB4\ (NJTRST).GPIO_Label=RELAY14
PB0.Signal=GPIO_Output
PA7.GPIOParameters=GPIO_Label
PA13\ (JTMS/SWDIO).Signal=SYS_JTMS-SWDIO
PA3.GPIO_Label=RELAY06
PB1.GPIOParameters=GPIO_Label
PA7.Signal=GPIO_Output
PB4\ (NJTRST).Signal=GPIO_Output

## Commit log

2024-05-25 First public release.

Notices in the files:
parts and their libraries:
WR-PHD: Copyright: Würth Elektronik
